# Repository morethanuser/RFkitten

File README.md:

# RFkitten

Full description here: http://morethanuser.blogspot.com/2016/08/cc1101-atmega32u-usb-dongle-python.html

Code is under MIT License, but watch out. Required libraries like e.g. LUFA has its own license.

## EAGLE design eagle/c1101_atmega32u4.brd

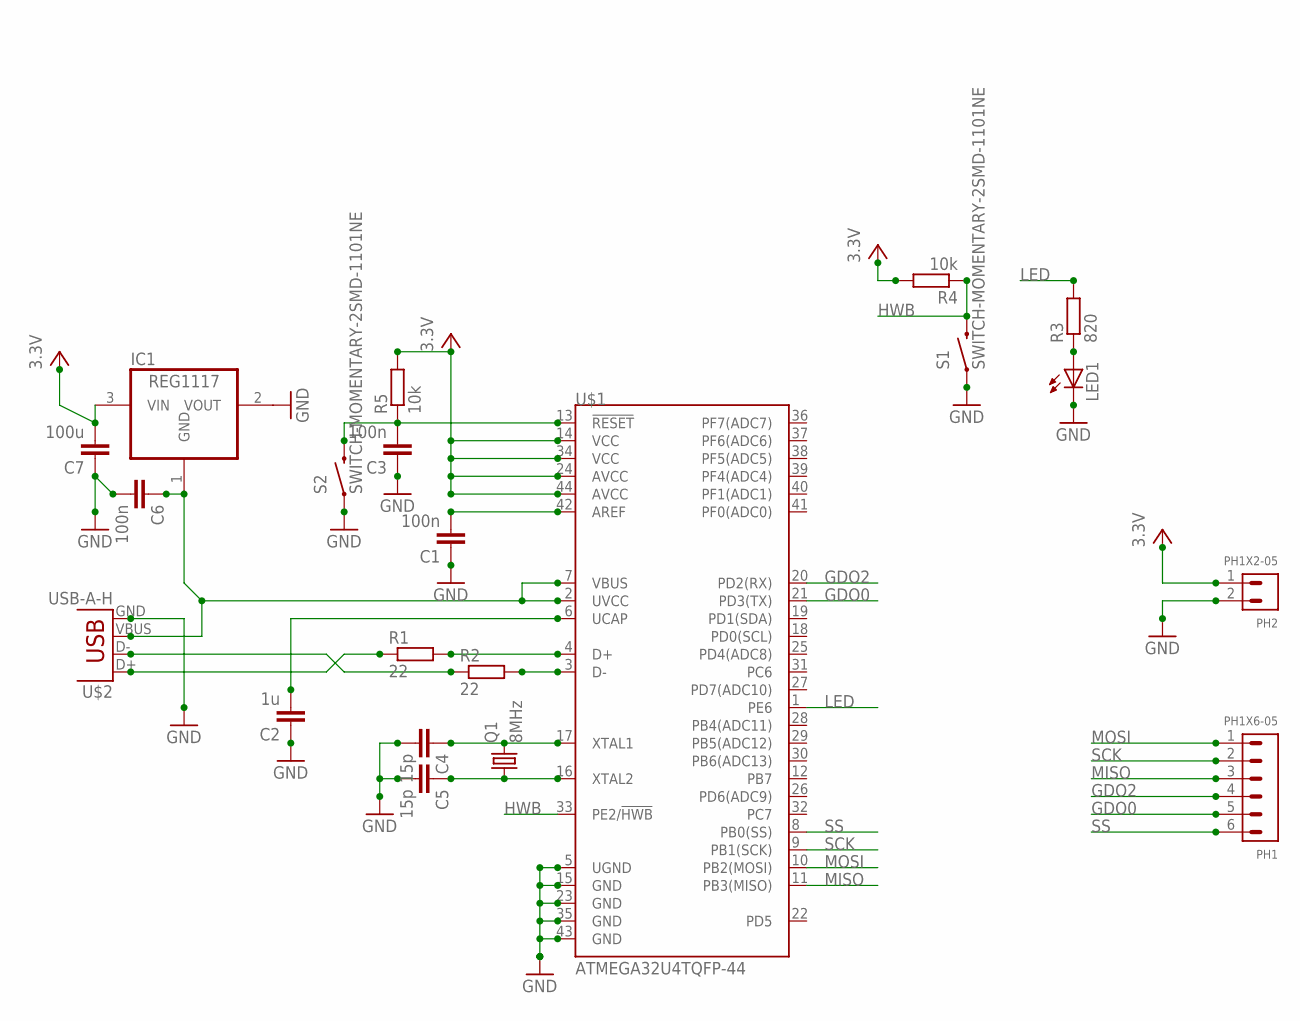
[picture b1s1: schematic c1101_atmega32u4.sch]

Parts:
C1, C3, C6: 100n; C0805
C2: 1u; C0805
C4, C5: 15p; C0805
C7: 100u; C0805
IC1: REG1117; SOT223
LED1: LEDCHIPLED_1206; CHIPLED_1206
PH1: PH1X6-05; PH005-1-6
PH2: PH1X2-05; PH005-1-2
Q1: 8MHz; HC49/S
R1, R2: 22; M0805
R3: 820; M0805
R4, R5: 10k; M0805
S1, S2: SWITCH-MOMENTARY-2SMD-1101NE; TACTILE-SWITCH-1101NE
U$1: ATMEGA32U4TQFP-44; TQFP44
U$2: USB-A-H

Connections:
GDO0: PH1.5, U$1.21 (PD3(TX))
GDO2: PH1.4, U$1.20 (PD2(RX))
GND: C1.1, C2.1, C3.1, C4.2, C5.2, C6.2, C7.1, IC1.2 (VOUT), LED1.C, PH2.2, S1.1, S2.1, U$1.5 (UGND), U$1.15 (GND), U$1.23 (GND), U$1.35 (GND), U$1.43 (GND), U$2.GND
HWB: R4.1, S1.2, U$1.33 (PE2/!HWB)
LED: R3.2, U$1.1 (PE6)
MISO: PH1.3, U$1.11 (PB3(MISO))
MOSI: PH1.1, U$1.10 (PB2(MOSI))
unnamed: R1.1, U$2.D+
unnamed: R2.1, U$2.D-
unnamed: R2.2, U$1.3 (D-)
unnamed: R1.2, U$1.4 (D+)
unnamed: C1.2, U$1.42 (AREF)
unnamed: C2.2, U$1.6 (UCAP)
unnamed: C3.2, R5.1, S2.2, U$1.13 (!RESET)
unnamed: C4.1, Q1.2, U$1.17 (XTAL1)
unnamed: C5.1, Q1.1, U$1.16 (XTAL2)
unnamed: LED1.A, R3.1
unnamed: C6.1, IC1.1 (GND), U$1.2 (UVCC), U$1.7 (VBUS), U$2.VBUS
SCK: PH1.2, U$1.9 (PB1(SCK))
SS: PH1.6, U$1.8 (PB0(SS))
VCC: C7.2, IC1.3 (VIN), PH2.1, R4.2, R5.2, U$1.14 (VCC), U$1.24 (AVCC), U$1.34 (VCC), U$1.44 (AVCC)

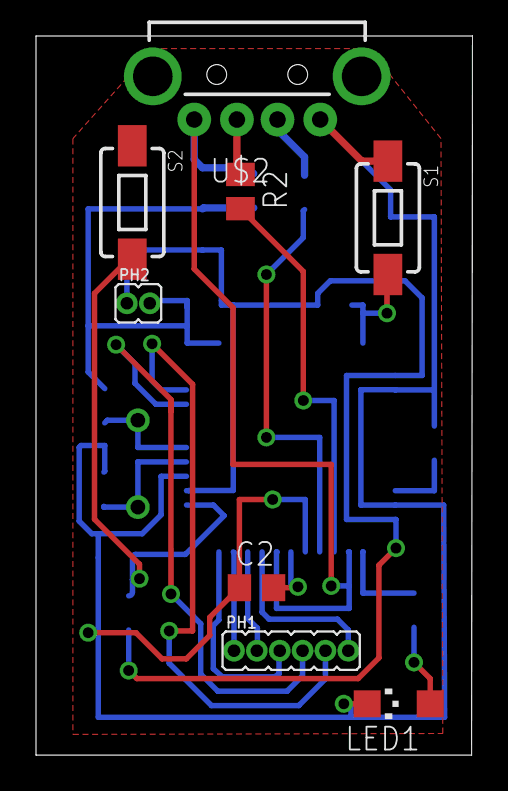
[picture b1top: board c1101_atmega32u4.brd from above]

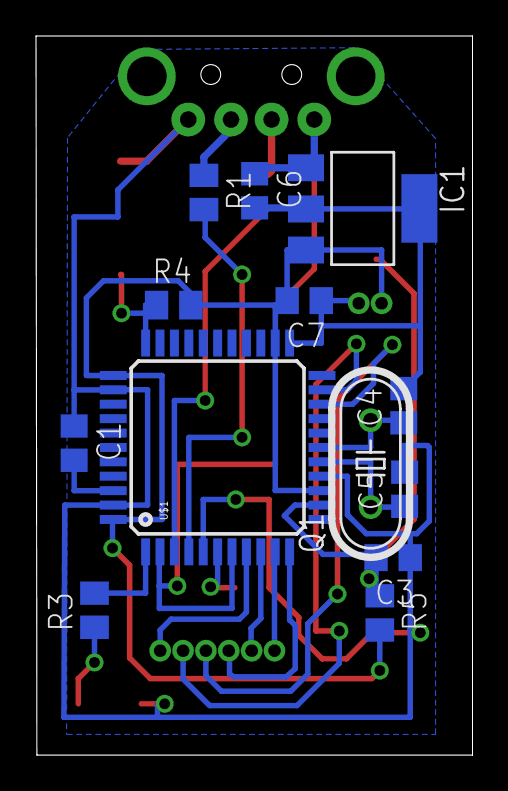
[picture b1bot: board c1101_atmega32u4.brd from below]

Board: 2 copper layers, 24.2 x 39.9 mm, 21 parts (13 on the bottom side), 21 nets.

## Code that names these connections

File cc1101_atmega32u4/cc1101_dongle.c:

#include "cc1101_dongle.h"
#include "usb_desc.h"

#include <avr/io.h>
#include <avr/wdt.h>
#include <avr/power.h>
#include <avr/interrupt.h>


struct spi_reg { 
   uint16_t reg;
   uint16_t val;
};


uint8_t spi_write(uint8_t data) {
   L(TIMSK0, TOIE0);
      SPDR = data;
      while(!(SPSR & (1 << SPIF)));
   H(TIMSK0, TOIE0);
   return SPDR;
}


uint8_t spi_strobe(uint8_t s) {
   uint8_t r = 0;
   ENABLE;
      r = spi_write(s);
   DISABLE;
   return r;
}


void spi_reg_write(struct spi_reg *r) {
   ENABLE;
      spi_write(r->reg | WRITE_BURST);
      spi_write(r->val);
   DISABLE;
}

void spi_patable_write(uint8_t *patable) {
   uint8_t i;
   ENABLE;
      spi_write(PATABLE | WRITE_BURST);
      for (i = 0; i < 8; i++)
         spi_write(patable[i]);

   DISABLE;
}



void spi_reg_read(struct spi_reg *r) {
   ENABLE;
      spi_write(r->reg | READ_BURST);
      r->val = spi_write(0);
   DISABLE;
}


uint8_t spi_reg_read_single(uint8_t a) {
   uint8_t r = 0;
   ENABLE;
      spi_write(a | READ_BURST);
      r = spi_write(0);
   DISABLE;
   return r;
}


USB_ClassInfo_CDC_Device_t serial = {
		.Config = {
				.ControlInterfaceNumber   = INTERFACE_ID_CDC_CCI,
				.DataINEndpoint           = {
						.Address          = CDC_TX_EPADDR,
						.Size             = CDC_TXRX_EPSIZE,
						.Banks            = 1,
					},
				.DataOUTEndpoint = {
						.Address          = CDC_RX_EPADDR,
						.Size             = CDC_TXRX_EPSIZE,
						.Banks            = 1,
					},
				.NotificationEndpoint = {
						.Address          = CDC_NOTIFICATION_EPADDR,
						.Size             = CDC_NOTIFICATION_EPSIZE,
						.Banks            = 1,
					},
			},
	};


void EVENT_USB_Device_Connect(void) { }
void EVENT_USB_Device_Disconnect(void) { }
void EVENT_USB_Device_ConfigurationChanged(void) { CDC_Device_ConfigureEndpoints(&serial); }
void EVENT_USB_Device_ControlRequest(void) { CDC_Device_ProcessControlRequest(&serial); }


uint8_t usb_cfg = 0;
void EVENT_CDC_Device_ControLineStateChanged(USB_ClassInfo_CDC_Device_t *const CDCInterfaceInfo) {
   L(EIMSK, INT2);
	usb_cfg = (CDCInterfaceInfo->State.ControlLineStates.HostToDevice & CDC_CONTROL_LINE_OUT_DTR) != 0;
}


void led_strobe() {
   static uint8_t strobe = 0;
   if(strobe) {
      strobe = 0;
      LED_ON;
   }
   else {
      LED_OFF;
      strobe = 1;
   }
}


uint8_t packet_len = 0;
uint8_t bytes_to_send = 0;

uint8_t buff[128] = {};
uint8_t buff_idx = 0;

uint8_t timer = 0;


ISR(TIMER0_OVF_vect) {  
   CDC_Device_USBTask(&serial);
   USB_USBTask();

   timer++;

   // blink led periodically
   if (timer > 40) {
      led_strobe();
      timer = 0;
   }
}  


// FIFO above threshold interrupt
ISR(INT2_vect) {
   volatile uint8_t val = spi_reg_read_single(RXBYTES);
   volatile uint8_t i = 0;

   ENABLE;
   spi_write(READ_BURST | RXFIFO);
   for(i = 0; i < (val & 0x7F); i++) {
      buff[buff_idx++] = spi_write(0);
   } 
   DISABLE;
   
   // this is only good for small data rates,
   // probably ring buffer would be better here
   for(i = 0; i < buff_idx; i++) {   
      CDC_Device_SendByte(&serial, buff[i]);
   }
   buff_idx = 0;

   CDC_Device_USBTask(&serial);
   USB_USBTask();
}



/****************************************************************************/
/*                                                                          */
/****************************************************************************/
int main()
{
   H(DDRE, PE6);  // led

   L(DDRD, PD2);  // GDO2
   L(DDRD, PD3);  // GDO0

   L(PORTD, PD2);
   L(PORTD, PD3);

   H(DDRB, PB0);  // SS
   H(DDRB, PB1);  // SCK
   H(DDRB, PB2);  // MOSI
   L(DDRB, PB3);  // MISO

   DISABLE;
   H(SPSR, SPI2X);
   H(SPCR, MSTR);
   H(SPCR, SPE);

	MCUSR &= ~(1 << WDRF);
	wdt_disable();
	clock_prescale_set(clock_div_1);
	USB_Init();

   H(TCCR0B, CS00);
   H(TCCR0B, CS02);
   H(TIMSK0, TOIE0);

   H(EICRA, ISC20);
   H(EICRA, ISC21);
   L(EIMSK, INT2);

   GlobalInterruptEnable();

   // reset CC1101
   DISABLE; 
   _delay_us(50);
   ENABLE; 
   spi_strobe(SRES);
   _delay_us(200);
   spi_strobe(SIDLE);
   spi_strobe(SFRX);
   spi_strobe(SFTX);

   int16_t c = 0;
   struct spi_reg r;
   uint8_t r_idx = 0;
   uint8_t pa_table[8] = { 0 };
   uint8_t pa_table_idx = 0;

   uint8_t state = 0;

	while(1) {
		c = CDC_Device_ReceiveByte(&serial);

      if (c < 0)
         continue;

      // if we have seen DTR before, push config into cc1101
      if (usb_cfg > 0) {

         if (usb_cfg == 1) {
             // first stage is to flush buffs and change cc1101 state
             // to idle
             usb_cfg = 2;

             spi_strobe(SIDLE);
             while(spi_reg_read_single(MARCSTATE) != MARCSTATE_IDLE);
             spi_strobe(SFRX);
//              while(spi_reg_read_single(MARCSTATE) != MARCSTATE_IDLE);
             spi_strobe(SFTX);
//              while(spi_reg_read_single(MARCSTATE) != MARCSTATE_IDLE);
             buff_idx = 0;

             for(pa_table_idx = 0; pa_table_idx < 8; pa_table_idx++)
               pa_table[pa_table_idx] = 0;
             pa_table_idx = 0;
         }

         // if we hit end of config 0xFF, back to normal operation, enable
         // fifo interrupt
         if (c == 0xff && r_idx == 0) {
            usb_cfg = 0;
            spi_strobe(SRX);
            while(spi_reg_read_single(MARCSTATE) != MARCSTATE_RX);
            H(EIMSK, INT2);
            continue;
         }

         if (r_idx == 0) {
            r.reg = c;
            r_idx++;
         } else {
            r.val = c;
            r_idx = 0;

            // in this special case, copy PKTLEN to variable
            if (r.reg == PKTLEN) {
               packet_len = r.val;
               bytes_to_send = packet_len;
            }

            if (r.reg == PATABLE) {
               if (pa_table_idx < 7) {
                  pa_table[pa_table_idx] = r.val;
                  pa_table_idx++;
               }
               else {
                  pa_table[pa_table_idx] = r.val;
                  spi_patable_write(pa_table);
            
                  for(pa_table_idx = 0; pa_table_idx < 8; pa_table_idx++)
                     pa_table[pa_table_idx] = 0;
                  pa_table_idx = 0;
               }

            } else {
               spi_reg_write(&r);
            }
         }

      } else {

         // we've got some data, push it to TX fifo, then
         // push over air
         ENABLE;
            spi_write(TXFIFO);
            spi_write(c);
         DISABLE;

         bytes_to_send--;

         if(bit_is_set(PIND, PD3) || bytes_to_send == 0) {
            spi_strobe(STX);

            do {
               state = spi_reg_read_single(MARCSTATE);
            } while(state != MARCSTATE_TXFIFO_UNDERFLOW && 
                    state != MARCSTATE_IDLE);

            spi_strobe(SFTX);
            while(spi_reg_read_single(MARCSTATE) != MARCSTATE_IDLE);
         }
         
         if (bytes_to_send == 0) {
            bytes_to_send = packet_len;
            spi_strobe(SRX);
            while(spi_reg_read_single(MARCSTATE) != MARCSTATE_RX);
         }
      }
   } 
}

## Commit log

2017-05-30 Initial code commit without LUFA
2017-05-30 readme
2017-05-30 Add LUFA placeholder
2017-05-30 Add other licenses info.
2017-05-30 Change name of atmega FW for something more clear
2017-06-10 Adding eagle files.

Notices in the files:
parts and their libraries:
SparkFun-DigitalIC: Licensing: Creative Commons ShareAlike 4.0 International - https://creativecommons.org/licenses/by-sa/4.0
